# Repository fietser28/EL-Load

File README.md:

<!--
SPDX-FileCopyrightText: 2023 Jan Nieuwstad <jan.sources@nieuwstad.net>

SPDX-License-Identifier: CC-BY-SA-4.0
-->

# Open-Source DC Electronic Load
A DC electronic load is used to simulate various load conditions on a power source by drawing a controlled amount of current or power. It is commonly used in testing power supplies, batteries, and other DC power devices to evaluate their performance, stability, and protection features.

# Overview

The DCL8010 electronic load module features a DC Electronic Load with several modes and protections.
This project is the for the development boards for this project. There is a seperate git project for the [firmware](https://github.com/fietser28/EL-Load-FW).

Together with [studio] and a BB3 there will be some example dashboards in the near future. For example a  application:

## Specifications

* Modes: Constant Current (CC), Constant Voltage (CV), Constant Power (CP) and Constand Resistance (CR). CC and CV are implemented in hardware, CP and CR are software controlled and have a slower dynamic response.
* Limits:
  * Current: 1mA - 10A set and read
  * Voltage: 0.5V - 80V (set), 1mV-80V read
  * Power: 80W

* Protections:
In hardware:
  * User definable Over Voltage Protection (OVP), clamps load off within 1ms
  * User definable Over Current Protection (OCP), clamps load off within 1ms
With software support:
  * User definable Over Power Protection for a specific time in seconds (1-99)
  * User definable Over Temperature Protection for a specific time in seconds (1-99)

* Other hardware features:
  * Von: The minimum voltage needs to be present before the load is turned on. This can be set with or without latching. This is implemented in hardware and when on guarentees a gradual turn-on if a power source is 'hot plugged' or turned on. 
  * Temperature based fan control
  * Fan RPM readout
  * Heatsink temperature readout

## Design considerations

### Sizing
The Electronic Load was designed to complement a pair of BB3 DCP405 modules. Such a pair can deliver up to 80V (series configuration) or 10A (parallel configuration). The power is just maximized what is achievable with the small form factor of a BB3 module.

Minimum set voltage (an von cutoff) aim is as low as possible but at least 0.5V. A low Von cutoff is important to discharge for example AA battries (around 0.8V).

### Resolution and accurary
Aim is to have 0.1% full scale accurary after calibration. Calibration will be done in 100% in software.

This results in the follwing goals:
| Input/output | Range      | Accuracy  | Resolution | Remarks 
| ---          |  ---       | ---       | ---        | ---
| Current monitor | 0-10A   | 10mA      | 1mA        | 
| Current monitor | 0-1A    | 1mA       | 0.1mA      | not evaluted/tested yet
| Voltage monitor | 0-80V   | 80mV      | 1mV        | Accuracy probably: 10mV
| Voltage monitor | 0-10V   | 1mV       | 0.1mV      | 
| Power measurements | 0-24h | 1s & 0.2% FS | 1s     | Perform accurate incremental calculations and timing
| Current set     | 5mA-10A   | 10mA      | 1mA        |
| Current set     | 5mA-1A  | 1mA       | 0.2mA      | 
| Voltage set     | 0.5-80V | 80mV      | 1mV        |
| Voltage set     | 0.5-9V  | 5mV       | 1mV        |
| Resistance set  | ?       | ?         | ?          | 0.5% FS In software
| Power set       | ?       | 0.25W     | ?          | 0.5% FS in software
| Von set (80V range) | 0.25-50V | 0.2V  | 0.1V       | Difficult to calibrate
| Von set (9V range) | 0.25-6V | 0.1V  | 0.1V       | Difficult to calibrate
| OCP (10A range) | 0.1-10A | 100mA  | 10mA       | Difficult to calibrate
| OCP set (1A range) | 0.25-6V | 10mA  | 1mA       | Difficult to calibrate, not implemnted yet
| OVP (80V range) | 1-80V | 0.2V  | 0.1V       | Difficult to calibrate
| OVP set (9V range) | 0.25-9V | 0.1V  | 0.1V       | Difficult to calibrate, not tested yet

Using 16bit ADC's and DAC's this should be achievable with calibration done in software.

### Hardware / software partitioning
Everything requiring a response below 10ms is implemented directly in hardware. All other functionality is preferably done in software.
This results in the following decisions:
* Current and Voltage measurement and control loops are in analog circuitry
* Over voltage and over current protection measurement and shutdown are in hardware with a seperate clamp on the power MOSFET gates to shutdown as fast as possible. It is up to software to toggle pins to release the hwardware protection
* Von circuitry is implemented in hardware including the latch. The Von circuitry is important to avoid the MOSFET loops to go fully open (unregulated) when the supplied current and/or voltage is less then the set values. An unregulated situation would lead to large (= overshoot) spikes if the DUT suddenly starts providing more power (e.g. plug-in/turn on).
* To combine current, voltage and Von control a cross-over circuit is used where the smallest set current will get priority.

### Fail safely: 
An electronic load is often used to discharge batteries and due to the time this takes it is not realistic to assume the discharge is always attended by a person. If a failing component in the electronic load fails it might cause a short. A battery (or other power source without proection) being shorted is a serious fire hazard. Therefore the Electronic Load has a physical fuse and all possbile components that might faile are behind this fuse. This includes the input snubber network, transient and revserse polarity diode and of course the main MOSFETS of the electronic load. This protection is not perfect: It requires a >10A peak surge, but greatly reduces the risk.

## Limitations / Issues

Most limitations,TODO's and issues are now tracked on [github issues](https://github.com/fietser28/EL-Load/issues).

# PCBs

### EL-Load-Analog
Main PCB. Contains all the analog circuitry including MOSFETS. The DAC & ADC's are also on this board. Sizes of the PCB adhere to DIB standard (I hope).

### EL-Load-Power-MCU
PCB for stand alone deployment outside of BB3. This board contains an isolated power supply (input 5V) with fan controllers, MCU, GPIO and a bunch of connectors. 
It directly fits to the Analog PCB with an addidional IDC cable. There is also an IDC connector to the Front panel PCB.

### EL-Load-Panel
Front panel PCB for standalone deployment. Connects to EL-Load-Power-MCU. Has a connector for common 2.4/2.8" TFT touchscreen PCBs, 1 encoder, 1 microswitch and one 1 LED.

## Obsolete PCB's

### EL-Load-Simple-Power
Obsolete test board. Very simple 78*/79* based power supply to generate 2x+12V, 1x+5V, 1x-5V and optionally -12V. Was used for previous version of EL-Load-Analog.

### EL-Load-Fan-Controller
Obsolete test board for the fan controller. For testing MAX31760 with 12V LDO regulation. Not used anymore. MAX31760 is now on Power-MCU-board.

### EL-Load-Digital
Obsolete test board for the MCU + ADC + DAC + GPIO + Touchscreen connection. DAC + ADC's are now on analog board. MCU and GPIO are now on new Power-MCU-board.

# Ownership and License

This work is licensed under multiple licences:
 * All hardware designs are licensed under CERN-OHL-W-2.0
 * All original software source code is licensed under GPL-3.0-or-later.
 * All documentation is licensed under CC-BY-SA-4.0.
 * There are also parts imported from other sources. See the indivdual files for there specific licenses.

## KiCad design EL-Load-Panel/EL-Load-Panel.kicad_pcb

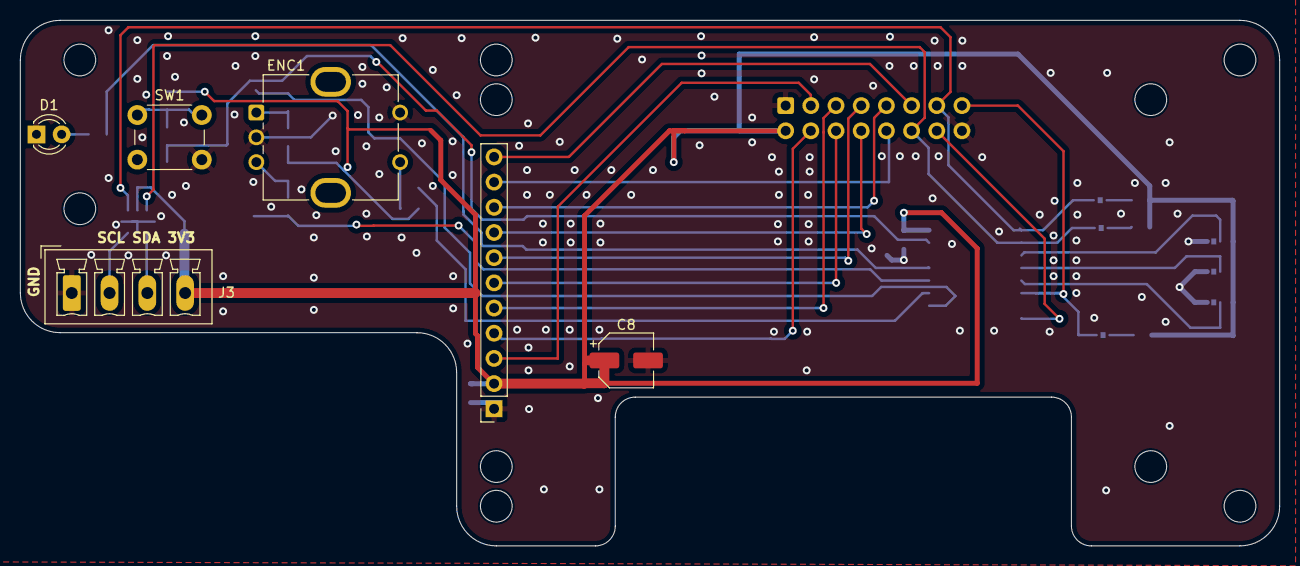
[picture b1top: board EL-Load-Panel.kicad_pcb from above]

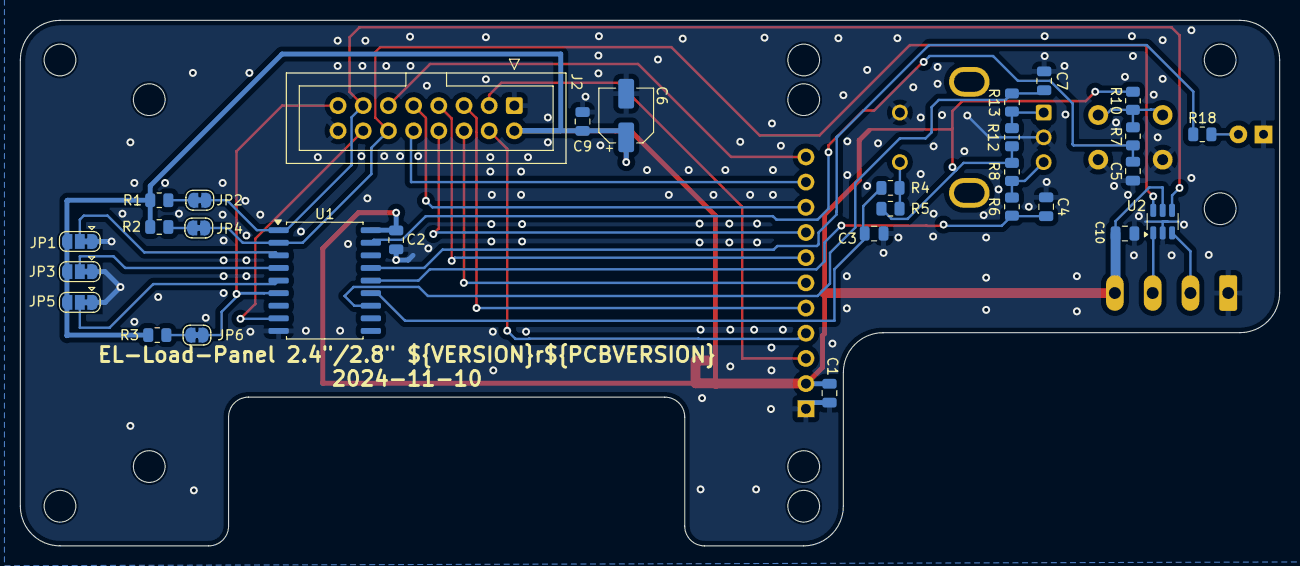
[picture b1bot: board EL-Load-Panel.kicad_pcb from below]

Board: 2 copper layers, 127.0 x 53.0 mm, 46 parts (30 on the bottom side), 33 nets.

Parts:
C1: 1u; C_0805_2012Metric
C2, C9, C10: 100n; C_0805_2012Metric
C3, C4, C5, C7: 10n; C_0805_2012Metric
C6, C8: 10u; CP_Elec_5x5.8
D1: LED; LED_D3.0mm
ENC1: Bourns PEC11R; RotaryEncoder_Bourns_Vertical_PEC12R-3x17F-Sxxxx
H1, H2, H3, H4, H5, H6, H7, H8, H9, H10: MountingHole; MountingHole_3.2mm_M3
J1: Touchscreen; PinSocket_1x11_P2.54mm_Vertical
J2: Conn_02x08_Odd_Even; IDC-Header_2x08_P2.54mm_Vertical
J3: Conn_01x04_Socket; PhoenixContact_MCV_1,5_4-G-3.81_1x04_P3.81mm_Vertical
JP1: A2; SolderJumper-3_P1.3mm_Bridged12_RoundedPad1.0x1.5mm
JP2: SCL PU; SolderJumper-2_P1.3mm_Bridged_RoundedPad1.0x1.5mm
JP3: A1; SolderJumper-3_P1.3mm_Bridged12_RoundedPad1.0x1.5mm
JP4: SDA PU; SolderJumper-2_P1.3mm_Bridged_RoundedPad1.0x1.5mm
JP5: A0; SolderJumper-3_P1.3mm_Bridged12_RoundedPad1.0x1.5mm
JP6: RST PU; SolderJumper-2_P1.3mm_Bridged_RoundedPad1.0x1.5mm
R1, R2, R3, R4, R5, R6, R7, R8, R10, R12, R13: 10k; R_0805_2012Metric
R18: 270; R_0805_2012Metric
SW1: ON/OFF; SW_PUSH_6mm_H8.5mm
U1: MCP23008-xSO; SOIC-18W_7.5x11.6mm_P1.27mm
U2: USBLC6-2SC6; SOT-23-6

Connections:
+3V3: C1.1, C2.1, C6.1, C8.1, C9.1, C10.1, J1.2, J2.2, J3.4, JP1.3 (B), JP3.3 (B), JP5.3 (B), R1.1, R2.1, R3.1, R5.1, R8.1, R10.1, R12.1, U1.18 (VDD), U2.5 (VBUS)
/A0: JP5.2 (C), U1.5 (A0)
/A1: JP3.2 (C), U1.4 (A1)
/A2: JP1.2 (C), U1.3 (A2)
/BLK: J1.7, J2.7
/CS1: J1.9, J2.9
/CS2: J1.10, J2.10
/DC: J1.6, J2.6
/INT: J2.14, U1.8 (INT)
/MISO: J1.8, J2.8
/MOSI: J1.4, J2.4
/PEN: J1.11, J2.11
/RESET: J1.5, J2.5
/SCL: J2.13, JP2.1 (A), U1.1 (SCL), U2.4 (I/O2)
/SCLK: J1.3, J2.3
/SDA: J2.12, JP4.1 (A), U1.2 (SDA), U2.6 (I/O1)
/encA: C7.1, R13.1, U1.12 (GP2)
/encB: C4.1, R6.1, U1.14 (GP4)
/encS: C3.1, R4.1, U1.13 (GP3)
/sw0: C5.1, R7.1, U1.17 (GP7)
/sw4: R18.1, U1.15 (GP5)
/~RESET: J2.15, JP6.1 (A), U1.6 (~RESET)
GND: C1.2, C2.2, C3.2, C4.2, C5.2, C6.2, C7.2, C8.2, C9.2, C10.2, D1.1 (K), ENC1.C, ENC1.S1, J1.1, J2.1, J2.16, J3.1, JP1.1 (A), JP3.1 (A), JP5.1 (A), SW1.2 (B), U1.9 (VSS), U2.2 (GND)
unnamed: D1.2 (A), R18.2
unnamed: ENC1.A, R12.2, R13.2
unnamed: ENC1.B, R6.2, R8.2
unnamed: ENC1.S2, R4.2, R5.2
unnamed: J3.2, U2.3 (I/O2)
unnamed: J3.3, U2.1 (I/O1)
unnamed: JP2.2 (B), R1.2
unnamed: JP4.2 (B), R2.2
unnamed: JP6.2 (B), R3.2
unnamed: R7.2, R10.2, SW1.1 (A)

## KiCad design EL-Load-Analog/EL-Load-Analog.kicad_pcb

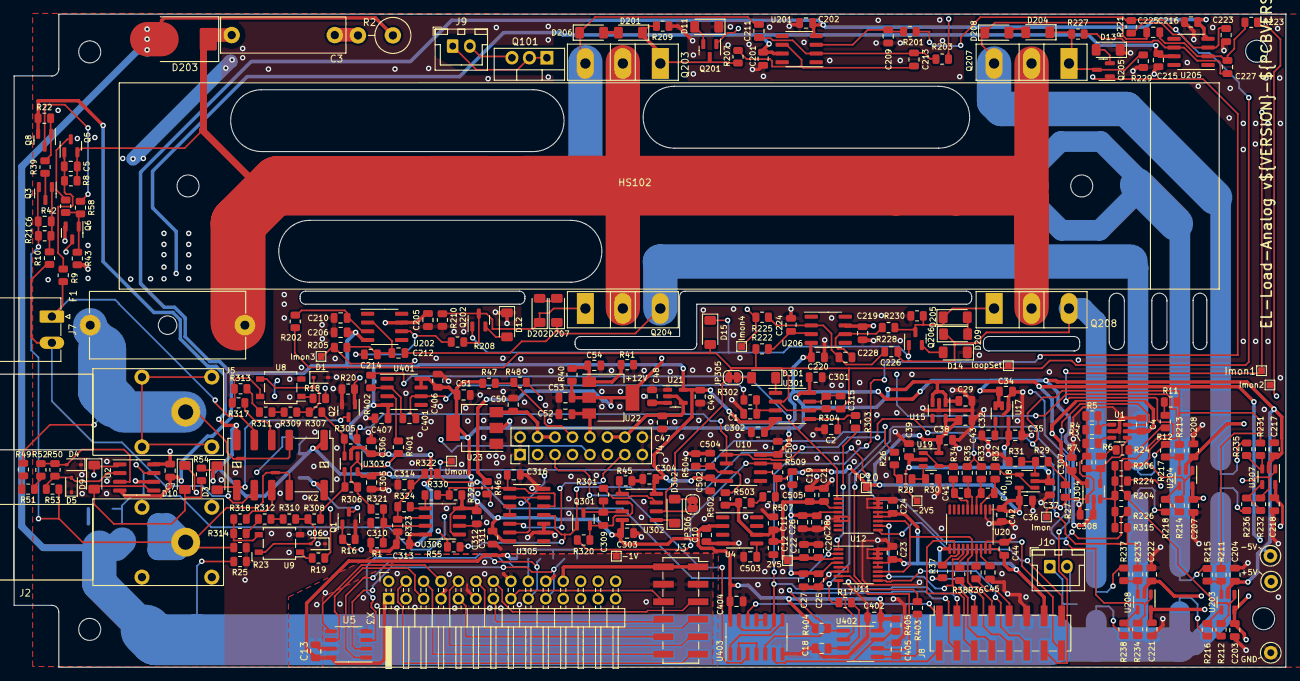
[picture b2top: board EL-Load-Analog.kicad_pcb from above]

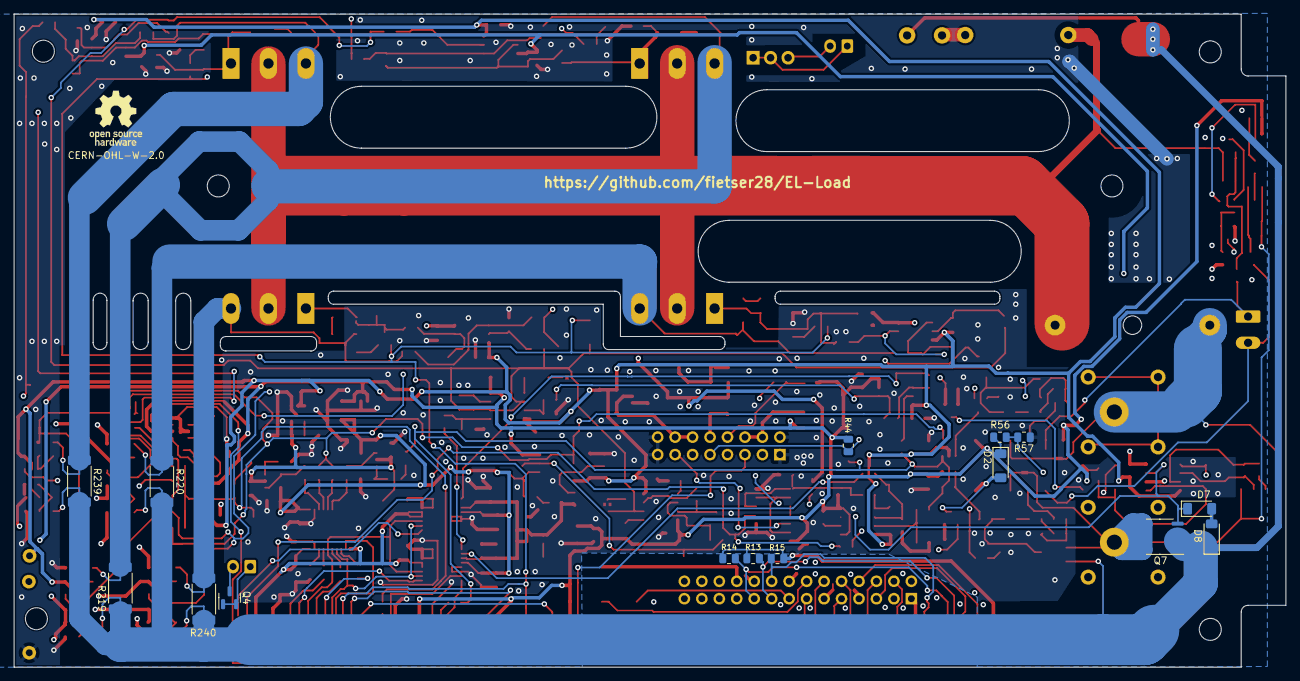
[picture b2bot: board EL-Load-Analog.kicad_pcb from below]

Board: 4 copper layers, 185.0 x 95.0 mm, 344 parts (16 on the bottom side), 198 nets.

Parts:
C1, C213, C214, C227, C228, C310: 1n; C_0805_2012Metric
C2: 33n; C_0805_2012Metric
C3: 100nF; C_Rect_L18.0mm_W5.0mm_P15.00mm_FKS3_FKP3
C4, C7, C13, C21, C22, C23, C24, C25, C26, C36, C37, C38, C39, C201, C202, C203, C204, C205, C206, C207, C208, C215, C216, C217, C218, C219, C220, C221, C222, C301, C302, C303, C304, C305, C306, C307, C308, C309, C311, C312, C313, C314, C402, C404, C406, C407, C501, C502, C504, C505: 100n; C_0805_2012Metric
C5, C6, C18, C40, C41, C43, C48, C54, C405: 10n; C_0805_2012Metric
C10, C12, C19, C20, C29, C32, C42, C44, C47, C503: 1u; C_0805_2012Metric
C11, C51, C53: 22u; C_0805_2012Metric
C27, C28, C49, C50, C52: 10u; C_0805_2012Metric
C34, C35, C316: 2u2; C_0805_2012Metric
C45: 220n; C_0805_2012Metric
C209, C210, C223, C224: 4n7; C_0805_2012Metric
C211, C212, C225, C226: 470p; C_0805_2012Metric
C315: 100p; C_0805_2012Metric
C401: 680n; C_0805_2012Metric
D1, D4, D5, D6: PESD3V3L1BAF; D_SOD-323
D2, D3, D9, D10, D11, D12, D13, D14, D15, D301, D302: 1N4148; D_MiniMELF
D7, D8, D201, D202, D204, D205, D206, D207, D208, D209: TZMB16-GS08; D_MiniMELF
D203: 1.5KE100A (smd); D_SMC
F1: Fuse; Fuseholder_Cylinder-5x20mm_Schurter_0031_8201_Horizontal_Op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
H101, H102, H103, H104: MountingHole; MountingHole_3.2mm_M3_DIN965
HS102: Heatsink; LAM3K
J1: Temp Sensor PCB; JST_XH_B2B-XH-A_1x02_P2.50mm_Vertical
J2: SWEB8094AU-SW; SWEB-8094-AU
J3: Conn_02x06_Odd_Even; PinSocket_2x06_P2.54mm_Vertical_SMD
J4: Conn_02x08_Odd_Even; PinHeader_2x08_P2.54mm_Vertical
J5: SWEB8094AU-RT; SWEB-8094-AU
J7: Conn_01x02_Socket; PhoenixContact_MC_1,5_2-G-3.81_1x02_P3.81mm_Horizontal
J8: Conn_02x08_Odd_Even; PinSocket_2x08_P2.54mm_Vertical_SMD
J9: Temp Sensor heatsink; JST_XH_B2B-XH-A_1x02_P2.50mm_Vertical
JP305: Jumper_2_Open; SolderJumper-2_P1.3mm_Bridged_RoundedPad1.0x1.5mm
JP306: Jumper_2_Open; SolderJumper-2_P1.3mm_Bridged2Bar_RoundedPad1.0x1.5mm
K2: EE2-5TNU; Relay_DPDT_Kemet_EE2_NU_DoubleCoil
NT201, NT202: NetTie_2; NetTie-2_SMD_Pad0.5mm
OSHWLogo1: CERN-OHL-W-2.0; OSHW-Logo_7.5x8mm_SilkScreen
Q1, Q2, Q201, Q202, Q205, Q206, Q301: 2N7002; SOT-23
Q3, Q6: MMBT5551; SOT-23
Q4: MMBT3904; SOT-23
Q5, Q8: MMBT5401; SOT-23
Q7: AOSP66923; SO-8_3.9x4.9mm_P1.27mm
Q101: TIP42C; TO-220-3_Vertical
Q203, Q204, Q207, Q208: IRFP250M; TO-247-3_Vertical
R1, R16, R20, R50, R53, R54, R321: 100k; R_0805_2012Metric
R2: 1k5 (3W); R_Axial_DIN0516_L15.5mm_D5.0mm_P5.08mm_Vertical
R3, R6, R315: 5k 0.1%; R_0805_2012Metric
R4, R5, R26, R29, R30, R31, R211, R212, R213, R214, R231, R232, R233, R234, R309, R310, R311, R312, R313, R314: 100k 0.1%; R_0805_2012Metric
R7: 50k 0.1%; R_0805_2012Metric
R8, R21: 330; R_0805_2012Metric
R9, R10: 750; R_0805_2012Metric
R11, R12, R23, R24, R25, R45, R221, R222: 0; R_0805_2012Metric
R13, R14, R15, R17, R46, R55, R56, R57, R201, R202, R403, R502, R507, R509: 10k; R_0805_2012Metric
R18, R19: 470; R_0805_2012Metric
R22, R43: 47k; R_0805_2012Metric
R27, R28, R305, R306: 10k 0.1%; R_0805_2012Metric
R32, R33, R34, R35, R322, R401, R402: 1k; R_0805_2012Metric
R36, R37, R38: 47; R_0805_2012Metric
R39, R42, R58, R203, R205, R223, R225: 22k; R_0805_2012Metric
R40: 200; R_0805_2012Metric
R41: 1k8; R_0805_2012Metric
R44, R47, R48: 4k7; R_0805_2012Metric
R49, R51, R52, R209, R210, R229, R230: 1M; R_0805_2012Metric
R204, R206, R224, R226: 20k 0.1%; R_0805_2012Metric
R207, R208, R227, R228: 100; R_0805_2012Metric
R215, R216, R217, R218, R235, R236, R237, R238: 1k1 0.1%; R_0805_2012Metric
R219, R220, R239, R240: 10m; R_2512_6332Metric_Pad1.40x3.35mm_HandSolder
R301, R302, R303, R304, R325, R404, R405: 2k; R_0805_2012Metric
R307, R308: 1k 0.1%; R_0805_2012Metric
R317, R318: 39k 0.1%; R_0805_2012Metric
R320: 7k5; R_0805_2012Metric
R323, R503: 15k; R_0805_2012Metric
R324: 24k; R_0805_2012Metric
R330: 2k2; R_0805_2012Metric
R504: 220; R_0805_2012Metric
TP1: -5V; TestPoint_Loop_D1.80mm_Drill1.0mm_Beaded
TP2: +5V; TestPoint_Loop_D1.80mm_Drill1.0mm_Beaded
TP3: GND; TestPoint_Loop_D2.50mm_Drill1.0mm
TP4: Imon3; TestPoint_Pad_1.0x1.0mm
TP5: Imon1; TestPoint_Pad_1.0x1.0mm
TP6: Imon4; TestPoint_Pad_1.0x1.0mm
TP7: Imon2; TestPoint_Pad_1.0x1.0mm
TP8: Imon; TestPoint_Pad_1.0x1.0mm
TP9: -2V5; TestPoint_Pad_1.0x1.0mm
TP10: 3V; TestPoint_Pad_1.0x1.0mm
TP11: -1V; TestPoint_Pad_1.0x1.0mm
TP12: 2V5; TestPoint_Pad_1.0x1.0mm
TP13: Umon; TestPoint_Pad_1.0x1.0mm
TP14: loopSet; TestPoint_Pad_1.0x1.0mm
U1: SN74LVC1G3157DBV; SOT-23-6
U2, U306, U402: LM393A; SOIC-8_3.9x4.9mm_P1.27mm
U4: REF5025AD; SOIC-8_3.9x4.9mm_P1.27mm
U5: 24LC32; SO-8_3.9x4.9mm_P1.27mm
U8, U9: VO1400AEFTR; SO-4_4.4x4.3mm_P2.54mm
U10: TL072/OPA2376; SOIC-8_3.9x4.9mm_P1.27mm
U11, U12: DAC8555; TSSOP-16_4.4x5mm_P0.65mm
U15: TPS7A2030; SOT-23-5
U17: TPS72325; SOT-23-5
U18, U19: MCP6V51; SOT-23-5
U20: ADS131M02; TSSOP-20_4.4x6.5mm_P0.65mm
U21: LT1964-5; TSOT-23-5
U22: AMS1117; SOT-223-3_TabPin2
U23: TLV1117-50; SOT-223-3_TabPin2
U201, U202, U205, U206: LM318D; SOIC-8_3.9x4.9mm_P1.27mm
U203, U204, U207, U208: MCP6V51/LTC2050HV; SOT-23-5
U301, U302: LM833; SOIC-8_3.9x4.9mm_P1.27mm
U303, U304: OPA189/MCP6V51/LTC2050HV; SOT-23-5
U305, U403: 74HCT02; SO-14_3.9x8.65mm_P1.27mm
U401: AD8038; SOIC-8_3.9x4.9mm_P1.27mm
X3: DIB Pheriperal connector

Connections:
+3.0VA: C25.1, C26.1, C27.1, C28.1, C32.1, C36.1, C38.1, C42.1, TP10.1, U11.4 (AVDD), U12.4 (AVDD), U15.5 (OUT), U18.5 (V+), U19.5 (V+), U20.1 (AVDD)
+3.3V-DIB: C13.1, R13.1, R14.1, R15.1, U5.8 (VCC), X3.1 (+3V3)
+3.3VD: C23.1, C24.1, C44.1, J8.13, U11.12 (IOVDD), U11.13 (~RST), U12.12 (IOVDD), U12.13 (~RST), U20.11 (~SYNC/RST), U20.20 (DVDD)
+5V: C4.2, C10.1, C29.1, C51.1, C203.2, C207.2, C218.2, C221.2, C301.2, C303.2, C305.2, C307.2, C311.2, C312.2, C402.2, C404.2, C406.2, C501.1, D2.1 (K), D3.1 (K), K2.1, K2.6, Q8.2 (E), R22.2, R44.2, R47.2, R54.2, R56.2, R325.1, R404.2, R405.2, TP2.1, U1.5 (V+), U4.2 (Vin), U10.8 (V+), U15.1 (IN), U15.3 (EN), U23.2 (VO), U203.5 (V+), U204.5 (V+), U207.5 (V+), U208.5 (V+), U301.8 (V+), U302.8 (V+), U303.5 (V+), U304.5 (V+), U305.14 (VCC), U306.5 (+), U306.8 (V+), U401.7 (V+), U401.8 (~CS), U402.8 (V+), U403.14 (VCC)
+5V-DIB: X3.23 (+5V), X3.24 (+5V)
+6V: C50.1, J4.4, J4.6, U23.3 (VI)
+12V: C7.2, C53.1, C201.2, C205.2, C215.2, C219.2, R40.1, R46.2, U2.8 (V+), U22.2 (VO), U201.7 (V+), U202.7 (V+), U205.7 (V+), U206.7 (V+)
+12V-DIB: J3.1, J3.2, X3.21 (+12V), X3.22 (+12V)
+15V: C52.1, J4.10, U22.3 (VI)
-1V: R320.2, R509.2, TP11.1, U10.7
-2V5: C35.2, C37.2, C39.2, TP9.1, U17.5 (OUT), U18.2 (V-), U19.2 (V-)
-5V: C7.1, C34.2, C49.2, C202.1, C204.1, C206.1, C208.1, C216.1, C217.1, C220.1, C222.1, C302.1, C304.1, C306.1, C308.1, C313.1, C407.1, C502.2, TP1.1, U2.4 (V-), U10.4 (V-), U17.2 (IN), U17.3 (EN), U21.5 (VOUT), U201.4 (V-), U202.4 (V-), U203.2 (V-), U204.2 (V-), U205.4 (V-), U206.4 (V-), U207.2 (V-), U208.2 (V-), U301.4 (V-), U302.4 (V-), U303.2 (V-), U304.2 (V-), U306.4 (V-), U401.4 (V-)
-6V: C47.2, J4.12, J4.14, U21.2 (VIN), U21.4 (~SHDN)
/CV, OVP & OCP/ReverseProt: D7.1 (K), Q7.4 (G), R46.1, U2.7
/DIB connection/DIB_A0: R13.2, U5.1 (A0), X3.17 (A0)
/DIB connection/DIB_A1: R14.2, U5.2 (A1), X3.19 (A1)
/DIB connection/DIB_A2: R15.2, U5.3 (A2), X3.18 (A2)
/DIB connection/DIB_CSA: J3.10, X3.9 (CSA)
/DIB connection/DIB_CSB: J3.7, X3.12 (CSB)
/DIB connection/DIB_IRQ: J3.9, X3.10 (IRQ)
/DIB connection/DIB_MISO: J3.5, X3.14 (MISO)
/DIB connection/DIB_MOSI: J3.6, X3.15 (MOSI)
/DIB connection/DIB_SCL: U5.6 (SCL), X3.5 (SSCL)
/DIB connection/DIB_SCLK: J3.8, X3.13 (SCLK)
/DIB connection/DIB_SDA: U5.5 (SDA), X3.8 (SSDA)
/DIB connection/DIB_SYNC: J3.12, X3.6 (SYNC)
/DIB connection/DIB_~RESET: J3.11, X3.4 (~RESET)
/MOSFET Loops/LoopImon: R204.2, R206.2, R224.2, R226.2, R315.1, U304.3 (+)
/MOSFET Loops/LoopIset: C315.2, D15.2 (A), JP305.1 (A), JP306.2 (B), R201.1, R202.1, R221.1, R222.1, R304.1, TP14.1, U301.2 (-), U301.6 (-), U302.2 (-)
/Monitoring, Crossover, Von/scaledUmon: C310.2, R1.2, R321.2, U306.3 (+)
ADC_CLK: J8.9, R36.2
ADC_CS: J8.6, U20.12 (~CS)
ADC_RDY: J8.5, R37.2
CVsetOut: C401.2, R302.2, U401.6
ClampOff: D15.1 (K), J8.3, Q201.1 (G), Q202.1 (G), Q205.1 (G), Q206.1 (G), U403.9, U403.13
CurrRangeLow: J8.14, U1.6
DAC1_CS: J8.12, U11.9 (~SYNC)
DAC2_CS: J8.15, U12.9 (~SYNC)
GCOM: R11.2, R33.1, R35.1, R211.2, R213.2, R231.2, R233.2, R305.2, R315.2, U10.1, U10.2 (-)
GND: C1.2, C2.2, C4.1, C10.2, C11.2, C12.2, C18.1, C19.2, C20.2, C21.2, C22.2, C23.2, C24.2, C25.2, C26.2, C27.2, C28.2, C29.2, C32.2, C34.1, C35.1, C36.2, C37.1, C38.2, C39.1, C42.2, C43.2, C44.2, C45.2, C47.1, C48.1, C49.1, C50.2, C51.2, C52.2, C53.2, C54.2, C201.1, C202.2, C203.1, C204.2, C205.1, C206.2, C207.1, C208.2, C209.1, C210.1, C215.1, C216.2, C217.2, C218.1, C219.1, C220.2, C221.1, C222.2, C223.1, C224.1, C301.1, C302.2, C303.1, C304.2, C305.1, C306.2, C307.1, C308.2, C310.1, C311.1, C312.1, C313.2, C314.1, C316.1, C402.1, C404.1, C405.1, C406.1, C407.2, C501.2, C502.1, C503.2, C504.2, C505.2, D1.2 (A2), D4.1 (A1), D5.1 (A1), D6.1 (A1), D11.1 (K), D12.1 (K), D13.1 (K), D14.1 (K), J2.MP (MountPin), J4.1, J4.2, J4.15, J4.16, J8.11, Q1.2 (S), Q2.2 (S), Q6.2 (E), R1.1, R16.1, R20.1, R23.2, R25.1, R30.2, R31.2, R41.2, R43.1, R45.2, R57.1, R209.2, R210.2, R229.2, R230.2, R323.2, R504.2, TP3.1, U1.2 (GND), U4.4 (GND), U8.2, U9.2, U10.5 (+), U11.5 (VREFL), U11.6 (GND), U11.14 (RSTSEL), U11.15 (~ENABLE), U11.16 (LDAC), U12.5 (VREFL), U12.6 (GND), U12.14 (RSTSEL), U12.15 (~ENABLE), U12.16 (LDAC), U15.2 (GND), U17.1 (GND), U20.2 (AGND), U20.19 (DGND), U21.1 (GND), U23.1 (GND), U305.2, U305.3, U305.7 (GND), U306.6 (-), U402.4 (V-), U403.7 (GND)
GND-DIB: C13.2, J3.3, J3.4, U5.4 (GND), U5.7 (WP), X3.7 (GND), X3.11 (GND), X3.16 (GND), X3.20 (GND), X3.25 (GND)
HWProtEnable: J4.5, U403.3
Imon: R3.2, R4.2, R5.2, R7.2, R27.1, R403.1, TP8.1, U304.1
Iset: R303.2, U11.1 (VOUTA)
LoadMin: D8.1 (K), D203.2 (A2), Q7.1 (S), Q7.2 (S), Q7.3 (S), R2.1, R25.2, R216.1, R218.1, R219.2, R220.2, R236.1, R238.1, R239.2, R240.2
LoadMinDirect: C6.1, J2.1, NT202.2, Q3.2 (E), Q7.5 (D), Q7.6 (D), Q7.7 (D), Q7.8 (D), R21.1, R23.1, R53.2
LoadMinMon: K2.10, NT202.1
LoadMinSense: J7.2, K2.8, R10.2
LoadPlus: C3.1, C5.2, D203.1 (A1), F1.2, Q5.2 (E), Q203.2 (D), Q204.2 (D), Q207.2 (D), Q208.2 (D), R8.2
LoadPlusMon: K2.3, NT201.1
LoadPlusSense: J7.1, K2.5, R9.1
LoadPlusUnfused: F1.1, J5.1, NT201.2, R49.1
unnamed: C3.2, R2.2
unnamed: C213.2, R207.1, U201.6
unnamed: C214.2, R208.1, U202.6
unnamed: C227.2, R227.1, U205.6
unnamed: C228.2, R228.1, U206.6
unnamed: C315.1, R304.2, U301.7
unnamed: C316.2, R325.2, R330.2, U305.5, U305.8
unnamed: D1.1 (A1), R307.2, R309.1, U8.3
unnamed: D2.2 (A), K2.12, Q1.3 (D)
unnamed: D3.2 (A), K2.7, Q2.3 (D)
unnamed: D4.2 (A2), R50.2, R52.2, U2.3 (+)
unnamed: D5.2 (A2), R50.1, R53.1, U2.2 (-)
unnamed: D6.2 (A2), R308.1, R310.2, U9.4
unnamed: D7.2 (A), D8.2 (A)
unnamed: D9.1 (K), R48.1, U2.1
unnamed: D9.2 (A), D10.2 (A), R54.1, U2.5 (+)
unnamed: D10.1 (K), R55.2
unnamed: D11.2 (A), Q201.2 (S)
unnamed: D12.2 (A), Q202.2 (S)
unnamed: D13.2 (A), Q205.2 (S)
unnamed: D14.2 (A), Q206.2 (S)
unnamed: D201.2 (A), D206.2 (A)
unnamed: D201.1 (K), Q201.3 (D), Q203.1 (G), R207.2, R209.1
unnamed: D202.2 (A), D207.2 (A)
unnamed: D202.1 (K), Q202.3 (D), Q204.1 (G), R208.2, R210.1
unnamed: D204.2 (A), D208.2 (A)
unnamed: D204.1 (K), Q205.3 (D), Q207.1 (G), R227.2, R229.1
unnamed: D205.2 (A), D209.2 (A)
unnamed: D205.1 (K), Q206.3 (D), Q208.1 (G), R228.2, R230.1
unnamed: C211.2, D206.1 (K), Q203.3 (S), R215.2, R219.1
unnamed: C212.2, D207.1 (K), Q204.3 (S), R217.2, R220.1
unnamed: C225.2, D208.1 (K), Q207.3 (S), R235.2, R239.1
unnamed: C226.2, D209.1 (K), Q208.3 (S), R237.2, R240.1
unnamed: D301.2 (A), JP305.2 (B)
unnamed: D301.1 (K), U301.1
unnamed: D302.2 (A), JP306.1 (A)
unnamed: D302.1 (K), U302.1
unnamed: J1.1, Q4.1 (B), Q4.2 (E)
unnamed: J1.2, Q4.3 (C)
unnamed: J9.1, Q101.1 (B), Q101.2 (C)
unnamed: J9.2, Q101.3 (E)
unnamed: K2.4, R317.2
unnamed: K2.9, R318.1
unnamed: C6.2, Q3.1 (B), R10.1, R21.2
unnamed: Q3.3 (C), R39.1
unnamed: C5.1, Q5.1 (B), R8.1, R9.2
unnamed: Q5.3 (C), R42.2
unnamed: Q6.1 (B), R42.1, R43.2, R58.1
unnamed: Q8.1 (B), R22.1, R39.2
unnamed: Q8.3 (C), R58.2
unnamed: C309.2, Q301.2 (S), R320.1, U302.6 (-)
unnamed: R3.1, U1.3
unnamed: R4.1, R5.1, U1.1
unnamed: R11.1, R12.2
unnamed: R12.1, R24.2
unnamed: R18.1, U8.1
unnamed: R19.1, U9.1
unnamed: R6.1, R24.1
unnamed: R26.2, R28.2
unnamed: R27.2, R29.2
unnamed: R49.2, R51.1
unnamed: R51.2, R52.1
unnamed: R203.2, R204.1, R212.2, TP5.1, U203.1
unnamed: R205.2, R206.1, R214.2, TP4.1, U204.1
unnamed: R223.2, R224.1, R232.2, TP7.1, U207.1
unnamed: R225.2, R226.1, R234.2, TP6.1, U208.1
unnamed: R309.2, R311.1
unnamed: R310.1, R312.2
unnamed: R311.2, R313.1
unnamed: R312.1, R314.2
unnamed: R313.2, R317.1, U8.4
unnamed: R314.1, R318.2, U9.3
unnamed: R503.2, R507.1
unnamed: R56.1, R57.2, U2.6 (-)
unnamed: C503.1, U4.5 (Trim/NR)
unnamed: C504.1, R502.2, R504.1, U10.3 (+)
unnamed: C505.1, R507.2, R509.1, U10.6 (-)
unnamed: C43.1, U17.4 (NR)
unnamed: R29.1, R31.1, U18.3 (+)
unnamed: R32.1, U18.1, U18.4 (-)
unnamed: R28.1, R30.1, U19.3 (+)
unnamed: R34.1, U19.1, U19.4 (-)
unnamed: C40.2, R33.2, U20.4 (AIN0N)
unnamed: C40.1, R32.2, U20.3 (AIN0P)
unnamed: C41.2, R35.2, U20.5 (AIN1N)
unnamed: C41.1, R34.2, U20.6 (AIN1P)
unnamed: C45.1, U20.18 (CAP)
unnamed: R36.1, U20.17 (CLKIN)
unnamed: R38.1, U20.15 (DOUT)
unnamed: R37.1, U20.13 (~DRDY)
unnamed: C48.2, U21.3 (BYP)
unnamed: C54.1, R40.2, R41.1, U22.1 (ADJ)
unnamed: C209.2, R201.2, U201.3 (+)
unnamed: C211.1, C213.1, R203.1, U201.2 (-)
unnamed: C210.2, R202.2, U202.3 (+)
unnamed: C212.1, C214.1, R205.1, U202.2 (-)
unnamed: R211.1, R215.1, U203.3 (+)
unnamed: R212.1, R216.2, U203.4 (-)
unnamed: R213.1, R217.1, U204.3 (+)
unnamed: R214.1, R218.2, U204.4 (-)
unnamed: C223.2, R221.2, U205.3 (+)
unnamed: C225.1, C227.1, R223.1, U205.2 (-)
unnamed: C224.2, R222.2, U206.3 (+)
unnamed: C226.1, C228.1, R225.1, U206.2 (-)
unnamed: R231.1, R235.1, U207.3 (+)
unnamed: R232.1, R236.2, U207.4 (-)
unnamed: R233.1, R237.1, U208.3 (+)
unnamed: R234.1, R238.2, U208.4 (-)
unnamed: C1.1, R302.1, U301.3 (+)
unnamed: C2.1, R303.1, U301.5 (+)
unnamed: R301.1, U302.3 (+)
unnamed: R45.1, U302.5 (+)
unnamed: R305.1, R307.1, U303.3 (+)
unnamed: R306.1, R308.2, U303.4 (-)
unnamed: R6.2, R7.1, U1.4, U304.4 (-)
unnamed: U305.10, U305.11
unnamed: U305.6, U305.9, U305.13
unnamed: C314.2, R322.2, R323.1, R324.2, U306.2 (-)
unnamed: R401.2, U401.3 (+)
unnamed: C401.1, R402.2, U401.2 (-)
unnamed: C18.2, R17.2, U402.3 (+)
unnamed: C405.2, R403.2, U402.5 (+)
unnamed: U403.1, U403.8
unnamed: U403.2, U403.4
unnamed: U403.10, U403.11
OCPset: U11.7 (VOUTC), U402.6 (-)
OCPtriggered: J8.2, R405.1, U402.7, U403.6
OVPset: U11.8 (VOUTD), U402.2 (-)
OVPtriggered: J8.4, R404.1, U402.1, U403.5
ReversePolarity: J4.8, R47.1, R48.2
SPI0_RX: J8.10, R38.2
SPI0_SCK: J8.8, U11.10 (SCLK), U12.10 (SCLK), U20.14 (SCLK)
SPI0_TX: J8.7, U11.11 (DIN), U12.11 (DIN), U20.16 (DIN)
SenseError: J4.9, Q6.3 (C), R44.1
Umon: R17.1, R26.1, R306.2, R321.1, R401.1, TP13.1, U303.1
Uset: R402.1, U12.1 (VOUTA)
VoltRangeLow: J4.11, R18.2, R19.2
VonComp: R324.1, R330.1, U306.1
VonOut: C309.1, Q301.3 (D), R301.2, U302.7
Vonset: R322.1, U11.2 (VOUTB)
Vref: C11.1, C12.1, C19.1, C20.1, C21.1, C22.1, R502.1, R503.1, TP12.1, U4.6 (Vout), U11.3 (VREFH), U12.3 (VREFH)
VsenseClear: J4.3, Q2.1 (G), R20.2
VsenseSet: J4.7, Q1.1 (G), R16.2
resetProt: J8.1, U403.12
~VonLatch: J4.13, U305.12
~Von: J8.16, Q301.1 (G), R55.1, U305.4

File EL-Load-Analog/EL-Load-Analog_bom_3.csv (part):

Description,Footprint,Part,Reference,Value,Quantity,Datasheet,Part Name,MPN,Sim.Device,Sim.Pins
"Unpolarized capacitor, small symbol",C_0805_2012Metric,C_Small,C315,100p,1,~,C_100.0pF_0805_20%,,,
"Unpolarized capacitor, small symbol",C_0805_2012Metric,C_Small,C213 C214 C227 C228,470p,4,~,C_470.0pF_0805_20%,,,
"Unpolarized capacitor, small symbol",C_0805_2012Metric,C_Small,C1 C310,1n,2,~,C_1.0nF_0805_20%,,,
"Unpolarized capacitor, small symbol",C_0805_2012Metric,C_Small,C5 C6 C18 C40 C41 C43 C48 C54 C405,10n,9,~,C_10.0nF_0805_20%,,,
"Unpolarized capacitor, small symbol",C_0805_2012Metric,C_Small,C2,33n,1,~,C_33.0nF_0805_20%,,,
"Unpolarized capacitor, small symbol",C_0805_2012Metric,C_Small,C4 C21 C22 C23 C24 C25 C26 C36 C37 C38 C39 C201 C202 C203 C204 C205 C206 C207 C208 C215 C216 C217 C218 C219 C220 C221 C222 C301 C302 C303 C304 C305 C306 C307 C308 C309 C311 C312 C313 C314 C402 C404 C406 C407 C501 C502 C504 C505,100n,48,~,C_100.0nF_0805_20%,,,
Unpolarized capacitor,C_Rect_L18.0mm_W5.0mm_P15.00mm_FKS3_FKP3,C,C3,100nF,1,~,C_100.0nF_15mm_THT_X2_10%,R46KI3100CKM1K,,
"Unpolarized capacitor, small symbol",C_0805_2012Metric,C_Small,C45,220n,1,~,C_220.0nF_0805_20%,,,
"Unpolarized capacitor, small symbol",C_0805_2012Metric,C_Small,C401,670n,1,~,,,,
"Unpolarized capacitor, small symbol",C_0805_2012Metric,C_Small,C10 C12 C19 C20 C29 C32 C42 C44 C47 C503,1u,10,~,C_1.0uF_0805_20%,,,
"Unpolarized capacitor, small symbol",C_0805_2012Metric,C_Small,C34 C35 C316,2u2,3,~,C_2.2uF_10V_X7R_10%_0805,,,
"Unpolarized capacitor, small symbol",C_0805_2012Metric,C_Small,C27 C28 C49 C50 C52,10u,5,~,C_10.0uF_25V_X7R_10%_0805,,,
"Unpolarized capacitor, small symbol",C_0805_2012Metric,C_Small,C11 C51 C53,22u,3,~,C_22u_16V_X5R_10%_0805,,,
"1500W unidirectional TRANSZORB® Transient Voltage Suppressor, DO-201AE",D_SMC,1.5KExxA,D203,1.5KE100A smd variant,1,https://www.vishay.com/docs/88301/15ke.pdf,D_1.5KE100A_SMC,,,
"100V 0.15A standard switching diode, DO-35",D_MiniMELF,1N4148,D2 D3 D301 D302,1N4148,4,https://assets.nexperia.com/documents/data-sheet/1N4148_1N4448.pdf,D_1N4148_miniMELF,,D,1=K 2=A
Zener diode,D_MiniMELF,D_Zener,D201 D202 D204 D205 D206 D207 D208 D209,TZMB16-GS08,8,~,D_Z_16V_miniMELF,,,
Fuse,Fuseholder_Cylinder-5x20mm_Schurter_0031_8201_Horizontal_Open,Fuse,F1,Fuse,1,~,,,,
Heatsink,LAM3K,Heatsink,HS102,Heatsink,1,~,,,,
"Generic connector, single row, 01x02, script generated","PhoenixContact_MC_1,5_2-G-3.81_1x02_P3.81mm_Horizontal",Conn_01x02_Socket,J7,Conn_01x02_Socket,1,~,H_Plug_2P_3.81MM_PCB_HOR,,,
"Generic connector, double row, 02x08, odd/even pin numbering scheme (row 1 odd numbers, row 2 even numbers), script generated (kicad-library-utils/schlib/autogen/connector/)",PinHeader_2x08_P2.54mm_Vertical,Conn_02x08_Odd_Even,J4,Conn_02x08_Odd_Even,1,~,H_Male_1x40_vertical_THT,,,
"Generic connector, double row, 02x08, odd/even pin numbering scheme (row 1 odd numbers, row 2 even numbers), script generated (kicad-library-utils/schlib/autogen/connector/)",PinSocket_2x08_P2.54mm_Vertical_SMD,Conn_02x08_Odd_Even,J8,Conn_02x08_Odd_Even,1,~,H_Female_2x8_SMD,,,
"Generic connectable mounting pin connector, single row, 01x01, script generated (kicad-library-utils/schlib/autogen/connector/)",SWEB-8094-AU,Conn_01x01_MountingPin,J5,SWEB8094AU-RT,1,~,H_Banana_Socket_24A_Red,,,
"Generic connectable mounting pin connector, single row, 01x01, script generated (kicad-library-utils/schlib/autogen/connector/)",SWEB-8094-AU,Conn_01x01_MountingPin,J2,SWEB8094AU-SW,1,~,H_Banana_Socket_24A_Black,,,
"Generic connector, single row, 01x02, script generated (kicad-library-utils/schlib/autogen/connector/)",JST_XH_B2B-XH-A_1x02_P2.50mm_Vertical,Conn_01x02,J1,Temp Sensor PCB,1,~,H_JST_XH_PCB_2P_VERT,,,
"Generic connector, single row, 01x02, script generated (kicad-library-utils/schlib/autogen/connector/)",JST_XH_B2B-XH-A_1x02_P2.50mm_Vertical,Conn_01x02,J9,Temp Sensor heatsink,1,~,H_JST_XH_PCB_2P_VERT,,,
"General purpose signal relay, Kemet EE2 Series, DPDT (2 Form C), double coil latching, SMD, 60W/125VA, 220VDC/250VAC, 2A, 5V DC coil",Relay_DPDT_Kemet_EE2_NU_DoubleCoil,EE2-5TNU,K2,EE2-5TNU,1,https://content.kemet.com/datasheets/KEM_R7002_EC2_EE2.pdf,ER_EE2-5TNU-L,,,
"0.115A Id, 60V Vds, N-Channel MOSFET, SOT-23",SOT-23,2N7002,Q1 Q2 Q201 Q202 Q205 Q206 Q301,2N7002,7,https://www.onsemi.com/pub/Collateral/NDS7002A-D.PDF,Q_2N7002,,,
"N-MOSFET transistor, gate/drain/source",TO-247-3_Vertical,Q_NMOS_GDS,Q203 Q204 Q207 Q208,IRFP250M,4,~,Q_IRFP250MPBF,,,
"0.2A Ic, 40V Vce, Small Signal NPN Transistor, SOT-23",SOT-23,MMBT3904,Q4,MMBT3904,1,https://www.onsemi.com/pdf/datasheet/pzt3904-d.pdf,Q_MMBT3904,,,
"-0.2A Ic, -40V Vce, Small Signal PNP Transistor, TO-92",SOT-23,MMBT5401,Q5,MMBT5401,1,,Q_MMBT5401,,,
"0.6A Ic, 160V Vce, General Purpose NPN Transistor, SOT-23",SOT-23,MMBT5551,Q3 Q6,MMBT5551,2,,Q_MMBT5551,,,
"-6A Ic, -100V Vce, Power PNP Transistor, TO-220",TO-220-3_Vertical,TIP42C,Q101,TIP42C,1,https://www.centralsemi.com/get_document.php?cmp=1&mergetype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,,,,
"Resistor, small symbol",R_0805_2012Metric,R_Small,R23 R45,0,2,~,R_0.0Ω_0805_1%,,,
Resistor,R_2512_6332Metric_Pad1.40x3.35mm_HandSolder,R,R219 R220 R239 R240,10m,4,~,R_R01_2512_1%_20ppmC,,,
"Resistor, small symbol",R_0805_2012Metric,R_Small,R36 R37 R38,47,3,~,R_47.0Ω_0805_1%,,,
"Resistor, small symbol",R_0805_2012Metric,R_Small,R39,91,1,~,R_91.0Ω_0805_1%,,,
"Resistor, small symbol",R_0805_2012Metric,R_Small,R207 R208 R227 R228,100,4,~,R_100.0Ω_0805_1%,,,
"Resistor, small symbol",R_0805_2012Metric,R_Small,R41 R504,220,2,~,R_220.0Ω_0805_1%,,,
"Resistor, small symbol",R_0805_2012Metric,R_Small,R32 R33 R34 R35 R322 R401 R402,1k,7,~,R_1.0kΩ_0805_1%,,,
"Resistor, small symbol",R_0805_2012Metric,R_Small,R40,1k8,1,~,R_1.8kΩ_0805_1%,,,
"Resistor, small symbol",R_0805_2012Metric,R_Small,R301 R302 R303 R304 R325 R404 R405,2k,7,~,R_2.0kΩ_0805_1%,,,
"Resistor, small symbol",R_0805_2012Metric,R_Small,R330,2k2,1,~,R_2.2kΩ_0805_1%,,,
"Resistor, small symbol",R_0805_2012Metric,R_Small,R320,7k5,1,~,R_7.5kΩ_0805_1%,,,
"Resistor, small symbol",R_0805_2012Metric,R_Small,R8 R17 R21 R42 R44 R201 R202 R221 R222 R403 R502 R507 R509,10k,13,~,R_10.0kΩ_0805_1%,,,
"Resistor, small symbol",R_0805_2012Metric,R_Small,R323 R503,15k,2,~,R_15.0kΩ_0805_1%,,,
"Resistor, small symbol",R_0805_2012Metric,R_Small,R9 R10 R22,22k,3,~,R_22.0kΩ_0805_1%,,,
"Resistor, small symbol",R_0805_2012Metric,R_Small,R324,24k,1,~,R_24.0kΩ_0805_1%,,,
"Resistor, small symbol",R_0805_2012Metric,R_Small,R43,47k,1,~,R_47.0kΩ_0805_1%,,,
"Resistor, small symbol",R_0805_2012Metric,R_Small,R16 R18 R19 R20 R203 R205 R223 R225 R321,100k,9,~,R_100.0kΩ_0805_1%,,,
"Resistor, small symbol",R_0805_2012Metric,R_Small,R209 R210 R229 R230,1M,4,~,R_1.0MΩ_0805_1%,,,
"Resistor, small symbol",R_0805_2012Metric,R_Small,R4 R5 R26 R27 R30 R31 R211 R212 R213 R214 R231 R232 R233 R234 R307 R308 R309 R310 R311 R312,100k 0.1%,20,~,R_100k_0805_0.1%,,,
"Resistor, small symbol",R_0805_2012Metric,R_Small,R28 R29 R305 R306,10k 0.1%,4,~,R_10k_0805_0.1%,,,
"Resistor, small symbol",R_0805_2012Metric,R_Small,R317 R318,1k 0.1%,2,~,R_1k_0805_0.1%,,,
"Resistor, small symbol",R_0805_2012Metric,R_Small,R215 R216 R217 R218 R235 R236 R237 R238,1k1 0.1%,8,~,R_1k1_0805_0.1%,,,
Resistor,R_Axial_DIN0516_L15.5mm_D5.0mm_P5.08mm_Vertical,R,R2,1k5 (3W),1,~,R_1.5kΩ_THT_15mm_5mm_3W_1%,FMP300FRF73-1K5,,
"Resistor, small symbol",R_0805_2012Metric,R_Small,R204 R206 R224 R226,20k 0.1%,4,~,R_20k_0805_0.1%,,,
"Resistor, small symbol",R_0805_2012Metric,R_Small,R313 R314,39k 0.1%,2,~,R_39k_0805_0.1%,,,
"Resistor, small symbol",R_0805_2012Metric,R_Small,R3 R6 R315,5k 0.1%,3,~,R_5k_0805_0.1%,,,
quad 2-input NOR gate,SO-14_3.9x8.65mm_P1.27mm,74HCT02,U305 U403,74HCT02,2,http://www.ti.com/lit/gpn/sn74hct02,U_74HCT02D,,,
"Single 2.7V to 6.0V Single Supply CMOS Op Amps, with Chip Select, SOIC-8",SOIC-8_3.9x4.9mm_P1.27mm,MCP603-xSN,U401,AD8038,1,http://ww1.microchip.com/downloads/en/DeviceDoc/21314g.pdf,U_AD8038ARZ,,,
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
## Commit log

2023-08-18 Put REF2025 in place, added LICENSES and .gitignore
2023-12-24 Added 3D models, mainly PCB stands
2023-12-24 Digital PCB update
2023-12-24 Major Analog PCB update DAC/ADC + connectors included, fan IC removed
2023-12-26 Added Power-MCU board
2023-12-26 Added EL-Load-Panel PCB
2023-12-26 Added standalone case 3D model
2023-12-26 Updated README, PNG's and PDF's
2023-12-26 small update
2023-12-26 Added Power-MCU schema PDF
2023-12-30 Added snubber on input, bananajacks, sense connector, some cleanup.
2023-12-30 added missing files
2023-12-30 Moved old PCBs to Obsolete directory
2024-01-05 Fixed Panel 1r1 and Power-MCU 2r2 versions
2024-01-05 BOM fixes/updates.
2024-01-26 Updated EL-Load-Panel to 1r2, fixing issues in issue #3.
2024-02-04 Added license text to panel, updated gitignore
2024-02-04 Fixes to Power-MCU board.
2024-02-04 Added SenseError detection (including ocmponents), added clearances, fixed few BOM items.
2024-02-06 Final v3 PCB version C.
2024-03-10 Final v3C version for Analog PCB.
2024-03-10 Updated README.md, issues/todo moved to github issues
2024-03-13 Updated due to #20
2024-03-15 Updated README.md based on #19 results
2024-03-20 Did #7, #10 and few items from #2
2024-03-20 Added +15VU led, fixed JP1
2024-03-21 Working on #4,#2 fixed #8,#22
2024-03-24 Fixing issues from #4, adding ESD protection (#6)
2024-03-30 Added heatsink moutingholes, reverse polarity, moved snubbers.
2024-04-21 Added Reverse Polarity Test PCB design
2024-06-21 New reverse polarity test schema & PCB.
2024-08-25 Added extra capacitor to Panel for stability. Upped schematic and pcb revisions to v2r3.
2024-09-28 Added inter board connector definitions (for V4)
2024-10-06 EL-Load-Power-MCU PCB v4r4 release.
2024-10-23 README update
2024-10-27 Connectors for v3 and v4 make explicit
2024-10-30 Fixed fan driver with jumper. Initial v5 version (still KiCad7)
2024-11-03 Standalone case for V4
2024-11-10 v4 Analog board design. Features reverse polarity, remote sense error and new clamping circuitry.
2025-01-03 Schema changed to 4.1, PCB version E. Modified R44, Remote sense error circtuit had wrong min input.
2025-01-12 Changed comparator to LM393A.
2025-02-22 3D model and bom update
2025-02-22 Initial Panel v3 commit
2025-07-27 standalone model cleanups and stl exports
2025-07-28 Added README with title and short description
    This is better now for SEO and people, who don't already know what an electonic load is.

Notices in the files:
EL-Load-Analog/EL-Load-Analog.kicad_pcb:
License: CERN-OHL-W-2.0
EL-Load-Power-MCU/EL-Load-Power-MCU.kicad_pcb:
License: ${LICENSE}
